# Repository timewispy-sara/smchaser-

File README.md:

# smchaser-
This is a simple LED chaser inspired by the LED chaser guided project so I can get the hang of designing PCBS! This was designed for Hack Club's Blueprint program.

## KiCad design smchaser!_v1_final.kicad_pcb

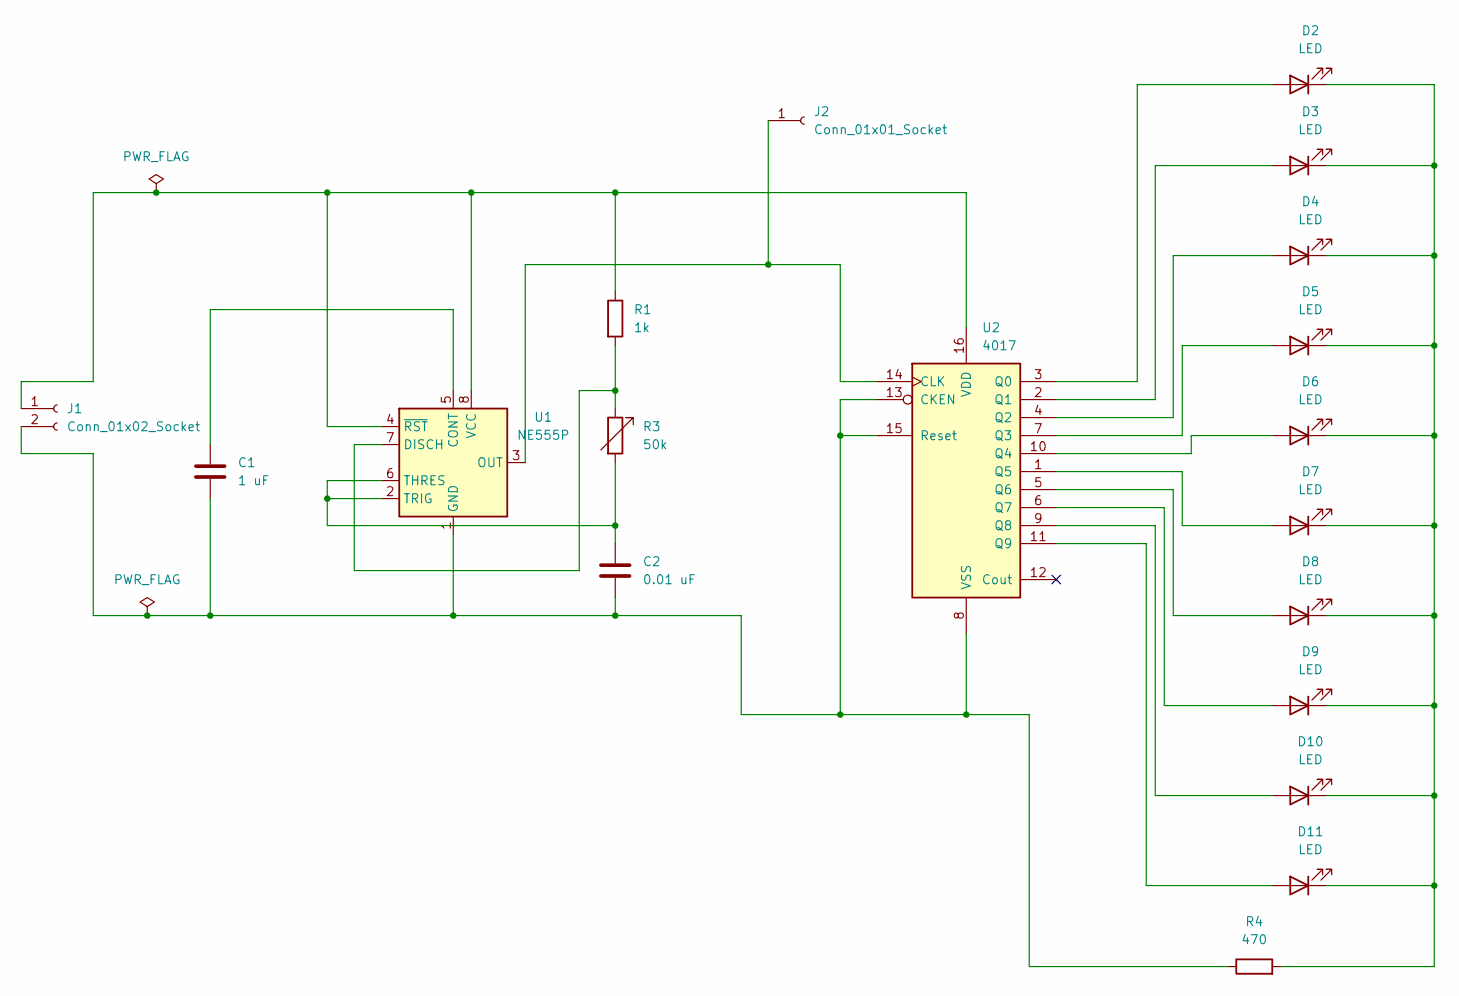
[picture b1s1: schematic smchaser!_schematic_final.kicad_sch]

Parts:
C1: 1 uF; CP_Radial_D5.0mm_P2.00mm
C2: 0.01 uF; C_Disc_D7.5mm_W2.5mm_P5.00mm
D2, D3, D4, D5, D6, D7, D8, D9, D10, D11: LED; LED_D3.0mm
J1: Conn_01x02_Socket; PinHeader_1x02_P2.54mm_Vertical
J2: Conn_01x01_Socket; PinSocket_1x01_P2.54mm_Vertical
R1: 1k; R_Axial_DIN0207_L6.3mm_D2.5mm_P7.62mm_Horizontal
R3: 50k; Potentiometer_Vishay_T93YA_Vertical
R4: 470; R_Axial_DIN0207_L6.3mm_D2.5mm_P7.62mm_Horizontal
U1: NE555P; DIP-8_W7.62mm
U2: 4017; N16

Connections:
unnamed: D2.2 (A), U2.3 (Q0)
unnamed: D3.2 (A), U2.2 (Q1)
unnamed: D4.2 (A), U2.4 (Q2)
unnamed: D5.2 (A), U2.7 (Q3)
unnamed: D6.2 (A), U2.10 (Q4)
unnamed: D7.2 (A), U2.1 (Q5)
unnamed: D8.2 (A), U2.5 (Q6)
unnamed: D9.2 (A), U2.6 (Q7)
unnamed: D10.2 (A), U2.9 (Q8)
unnamed: D2.1 (K), D3.1 (K), D4.1 (K), D5.1 (K), D6.1 (K), D7.1 (K), D8.1 (K), D9.1 (K), D10.1 (K), D11.1 (K), R4.2
unnamed: D11.2 (A), U2.11 (Q9)
unnamed: J1.1, R1.1, U1.4 (~RST), U1.8 (VCC), U2.16 (VDD)
unnamed: C1.2, C2.2, J1.2, R4.1, U1.1 (GND), U2.8 (VSS), U2.13 (CKEN), U2.15 (Reset)
unnamed: J2.1, U1.3 (OUT), U2.14 (CLK)
unnamed: C1.1, U1.5 (CONT)
unnamed: R1.2, R3.1, U1.7 (DISCH)
unnamed: C2.1, R3.2, U1.2 (TRIG), U1.6 (THRES)

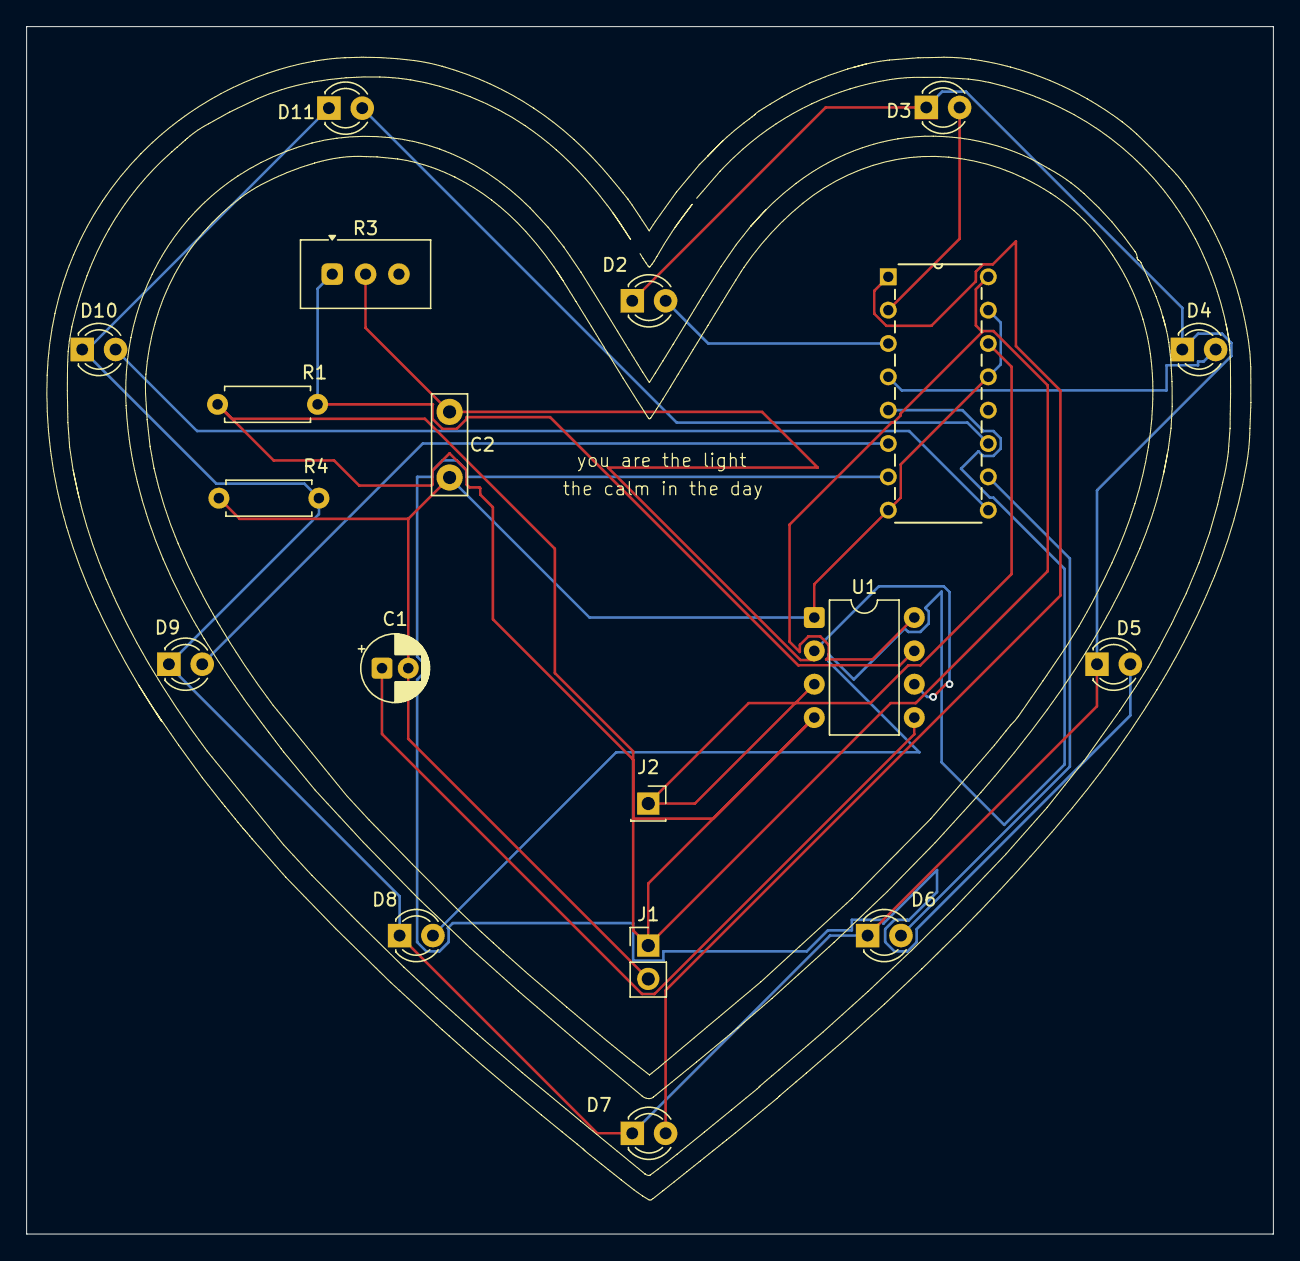
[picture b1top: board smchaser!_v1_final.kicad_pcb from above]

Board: 2 copper layers, 95.0 x 92.0 mm, 19 parts (0 on the bottom side), 17 nets.

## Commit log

2026-04-02 Create placeholder
2026-04-02 gerber file renaming
